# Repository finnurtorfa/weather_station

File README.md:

Weather Station
======

This is a git repository for the firmware and hardware of a weather station.

Specification:
----

The weather station should have the following capabilities:

- [x] Temperature measurement
- [x] Anemometer
- [ ] Wind direction measurement
- [x] Humidity measurement
- [x] Barometer 
- [x] Bluetooth Low Energy
- [ ] Serial communication
- [x] Battery powered

## Microcontroller

The microcontroller chosen to power the weather station is the Nordic
Semiconductor nRF51422 multiprotocol system on a chip microcontroller. It's key
features include

- 2.4 GHz transceiver
- ARM Cortex-M0 32 bit processor
- 256 or 128 kB flash program memory
- 16 or 32 kB RAM
- 31 GPIO pins
- 32 bit and 16 bit timers
- SPI
- TWI(I2C)
- 8-10 bit ADC
- UART
- Programmable Peripheral Interconnect
- Real Time Counter

It comes in a variety of packages, but the package chosen is the QFN48 package.
It also has quite flexible power management and can be supplied by voltage in
the range of 1.8V to 3.6V.

## Crystal

The crystal chosen for this project is the FA-20H series 16 MHz crystal by
EPSON. It has a frequency stability of +-10ppm, 8pF load capacitance and 80 Ohm
ESR. Following Nordic Semiconductor's white paper on selecting load capacitors
with the crystal and guestimating the stray pcb capacitance as ~3 pF we select C1=C2=12pF

## Voltage regulator

The regulator chosen to supply power to the MCU is LM3668 buck/boost dc-dc
converter by Texas Instruments. It is a single inductor converter with high
efficiency(~90% for loads from approx 3-4 mA - few hundred mA in auto mode),
making it ideal to power the nRF51 devices from a single LiPo cell.

## Battery charging

The MCP73831 single cell LiIon/LiPo battery charge management controller was
chosen for the task of charging the battery from USB(5V) power source.

## Temperature Sensor

The TMP112 digital temperature sensor has a temperature operating range from
-40°C - +125°C. It has an accuracy of 0.5% or 1% depending on the operating
range and a resolutionof 12 bits. It communicates with the host MCU via I2C.

## Humidity Sensor

The Si7013 is a humidity and temperature sensor with an operating range from
0-100% in relative humidity and -40°C - +125°C. It has an accuracy of +-3%
relative humidity and +-0.4°C for temperature and communicates with a host MCU
through I2C. 

## Barometer sensor

The BMP280 is a barometer that has a pressure range from ~300-1100hPa with
typical accuracy of +-1 hPa. It communicates with a host MCU through either I2C
or SPI.

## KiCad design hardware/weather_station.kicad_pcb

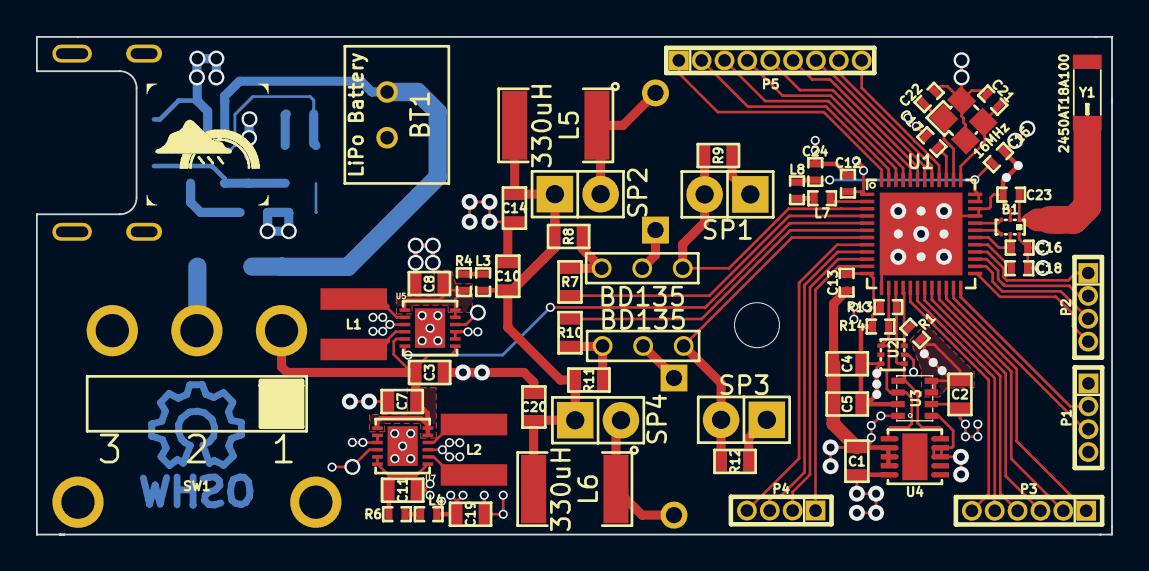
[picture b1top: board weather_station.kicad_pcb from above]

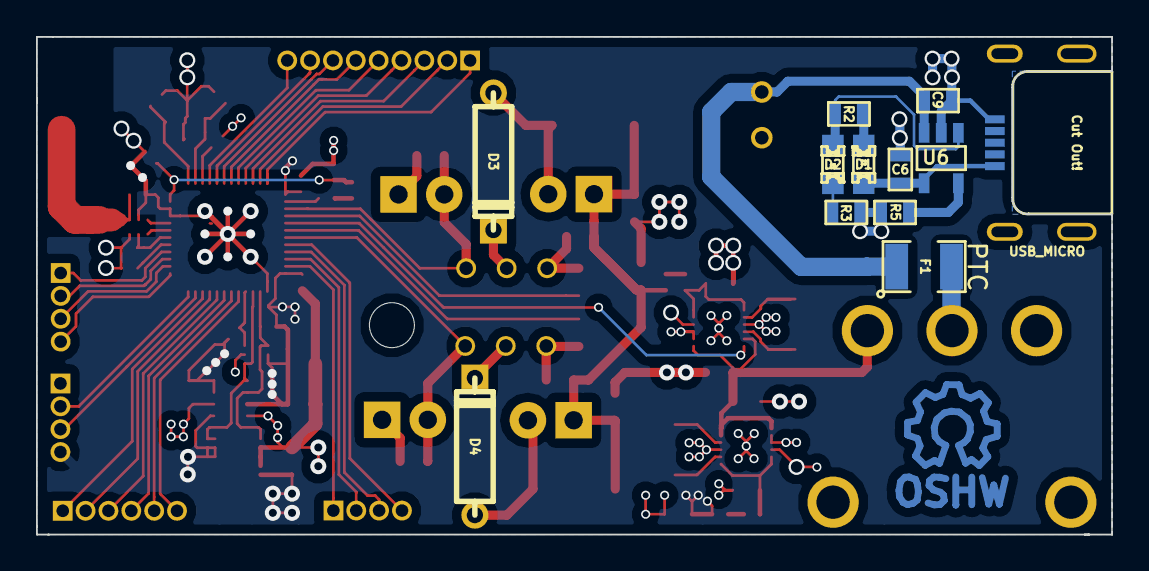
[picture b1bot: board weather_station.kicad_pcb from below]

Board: 4 copper layers, 59.7 x 27.6 mm, 78 parts (13 on the bottom side), 69 nets.

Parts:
B1: 2450BM14E0003; 2450BM14E0003Balun
BT1: LiPo Battery; JST_2_54
C1, C2, C4, C5, C10, C19: 100nF; SMD-0603
C3, C7: 10uF; SMD-0603
C6, C9: 4.7uF; SMD-0603
C8, C11, C14, C20: 22uF; SMD-0603
C12, C17: 100nF; SMD-0402
C13: 4.7uF; SMD-0402
C15: 1nF; SMD-0402
C16: 2.2nF; SMD-0402
C18: 47nF; SMD-0402
C21, C22: 12pF; SMD-0402
C23: 2pF; SMD-0402
C24: 1uF; SMD-0402
D1: RED; LED-0805
D2: GREEN; LED-0805
D3, D4: 1N4007; DO-41
F1: PTC; SMD-1210
J1: USB_MICRO; USB_MICRO_B
L1, L2: 2.2uH; SMD_4040
L3, L4: 52nH; SMD-0402
L5, L6: 330uH; SMD-1812
L7: 10uH; SMD-0402
L8: 15nH; SMD-0402
MountingHole_2-5mm: VAL**; MountingHole_2-5mm
P1, P2, P4: CONN_01X04; 4PIN_1.27MMP
P3: CONN_01X06; 6PIN_1.27MMP
P5: CONN_01X09; 9PIN_1.27MMP
Q1, Q2: BD135; TO-126
R1, R13, R14: 4K7; SMD-0402
R2, R3: 470R; SMD-0603
R4, R6: 10R; SMD-0402
R5: 2K; SMD-0603
R7, R10: 3K3; SMD-0603
R8, R11: 10K; SMD-0603
R9, R12: 33K; SMD-0603
SP1: SOUTH; Pin_Header_Straight_1x02
SP2: NORTH; Pin_Header_Straight_1x02
SP3: WEST; Pin_Header_Straight_1x02
SP4: EAST; Pin_Header_Straight_1x02
SW1: SWITCH_SPDT; T511006_SPDT
Symbol_OSHW-Logo_CopperTop: VAL**; Symbol_OSHW-Logo_CopperTop
U1: nRF51x22; nRF51_QFN48_HandSolder
U2: TMP112; SOT-563
U3: BMP280; LGA_2x2.5x0.95
U4: Si7013; DFN10_3x3
U5, U7: LM3668; WSON12_0.4P
U6: MCP73831; SOT-23-5-CUSTOM
X1: 16MHz; CRYSTAL_SMD2520
Y1: 2450AT18A100; 2450AT18A100E
weather_logo: weather_logo

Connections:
ALERT: R1.2, U1.16, U2.3
ANT1: B1.4, U1.31
ANT2: B1.3, U1.32
AVDD: C15.1, C24.1, L8.2, U1.35, U1.36
DCC: L7.1, U1.2
GND: B1.2, B1.6, BT1.2, C1.1, C2.1, C3.2, C4.2, C5.1, C6.2, C7.2, C8.2, C9.2, C10.2, C11.2, C12.2, C13.2, C14.2, C15.2, C16.1, C17.2, C18.2, C19.2, C20.2, C21.2, C22.1, C23.1, C24.2, J1.5, P1.4, R3.1, R5.1, R9.1, R12.1, SP1.1, SP3.1, U1.13, U1.33, U1.34, U2.2, U3.1, U3.7, U4.2, U4.3, U4.4, U5.3, U5.8, U5.9, U5.10, U5.~, U6.2, U7.3, U7.8, U7.9, U7.10, U7.~, X1.3
unnamed: B1.1, C23.2, Y1.1
unnamed: C6.1, D1.1, J1.1, U6.4
unnamed: C8.1, R4.2, U5.1, U5.11, U5.12
unnamed: C11.1, R6.2, U7.1, U7.11, U7.12
unnamed: C17.1, U1.39
unnamed: C18.1, U1.29
unnamed: D1.2, R2.1
unnamed: D2.1, R2.2, U6.1
unnamed: D2.2, R3.2
unnamed: D3.1, L5.1, SP2.2
unnamed: D3.2, Q1.2
unnamed: D4.1, L6.1, SP4.2
unnamed: D4.2, Q2.2
unnamed: F1.2, SW1.2
unnamed: L1.1, U5.2
unnamed: L1.2, U5.4
unnamed: L2.1, U7.2
unnamed: L2.2, U7.4
unnamed: L3.1, R4.1
unnamed: L4.1, R6.1
unnamed: L7.2, L8.1
unnamed: Q1.3, R7.1, R8.2
unnamed: Q2.3, R10.1, R11.2
unnamed: R5.2, U6.5
P0.04: P4.1, U1.8
P0.05: P4.2, U1.9
P0.06: P4.3, U1.10
P0.07: P4.4, U1.11
P0.11: P3.1, U1.17
P0.12: P3.2, U1.18
P0.13: P3.3, U1.19
P0.14: P3.4, U1.20
P0.15: P3.5, U1.21
P0.16: P3.6, U1.22
P0.17: P2.1, U1.25
P0.18: P2.2, U1.26
P0.19: P2.3, U1.27
P0.20: P2.4, U1.28
P0.21: P5.1, U1.40
P0.22: P5.2, U1.41
P0.23: P5.3, U1.42
P0.24: P5.4, U1.43
P0.25: P5.5, U1.44
P0.26: P5.6, U1.45
P0.27: P5.7, U1.46
P0.28: P5.8, U1.47
P0.29: P5.9, U1.48
PULSE1: Q1.1, R9.2, SP1.2, U1.3
PULSE2: Q2.1, R12.2, SP3.2, U1.7
PWM1: R7.2, U1.4
PWM2: R10.2, U1.6
SCL: R13.2, U1.15, U2.1, U3.4, U4.10
SDA: R14.2, U1.14, U2.4, U3.3, U4.1
SWDCLK: P1.3, U1.24
SWDIO: P1.2, U1.23
V3.3: C1.2, C2.2, C4.1, C5.2, C12.1, C13.1, C19.1, L4.2, P1.1, R1.1, R13.1, R14.1, U1.1, U1.12, U2.5, U2.6, U3.2, U3.5, U3.6, U3.8, U4.5, U4.8, U4.9
V5.0: C10.1, C14.1, C20.1, L3.2, L5.2, L6.2, R8.1, R11.1, SP2.1, SP4.1
V50_EN: U1.5, U5.6
VBAT: BT1.1, C9.1, F1.1, U6.3
VDD_PA: B1.5, C16.2, U1.30
VIN: C3.1, C7.1, SW1.1, U5.5, U5.7, U7.5, U7.6, U7.7
XC1: C21.1, U1.37, X1.2
XC2: C22.2, U1.38, X1.1

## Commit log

2015-03-27 Initial commit
    Add the README.md with the initial specification of the project and some description of
    the MCU chosen for the project.
2015-03-27 Datasheet and Product Anomaly Notification for MCU
    The MCU chosen is the nRF51422. Add the Product Specification and Product
    Anomaly Notification for it under reading material.
2015-03-27 KiCad project file
    Initialize the KiCad project.
2015-03-27 Add an empty schematic
2015-03-27 Add a ignore rules file for the hardware
    Ignore cache library files and backup files.
2015-03-27 Add a datasheet for LM3668 dc-dc regulator
    LM3668 is a 1A, High-Efficiency Dual-Mode Single-Inductor Buck-Boost DC-DC
    Converter.
2015-03-27 Application Note for LM3668 dc-dc regulator
2015-03-27 Add a nRF51x22 schematic symbol
2015-03-27 Add a battery to the schematic
    Along with a BAT+ label.
2015-03-28 Voltage regulator circuitry
    Add circuitry for the voltage regulator. The regulator chosen for the task is
    the LM3668 Buck/Boost converter by Texas Instruments. Also add a SPDT switch and
    a polyfuse to protect the circuitry against accidental short circuits.
2015-03-28 Datasheet for a SPDT switch.
    Add the datasheet for the chosesn SPDT switch. A 500 series right angle
    miniature slide switch.
2015-03-28 Add a spec sheet for the power inductor
    A 2.2 uH power inductor chosen for the LM3668 buck/boost converter.
2015-03-28 Add battery charging circuit
    Add circuitry around the MCP73831 linear charge management controller.
2015-03-28 Add decoupling circuitry and external LC filter
2015-03-28 Add circuitry for the 16MHz crystal
2015-03-28 Add a whitepaper about crystal oscillator circuitry
2015-03-29 Add datasheet for the crystal
2015-03-29 Move decoupling components around
2015-03-29 Add a datasheet for MCP73831 battery charge management controller
2015-03-29 Update the README with the core components
2015-03-29 Add datasheet for balun and antenna
    The balun is specifically designed for use with nRF51 devices.
2015-03-29 Add balun and an antenna to schematic
2015-03-30 Add TMP112 to the schematic and pull-up for TWI
    TMP112 is a temperature sensor made by Texas Instruments.
    Please note with the pull-up resistors that internally the GPIO pins of the
    nRF51 can be configured with an pull-up resistance of ~13K Ohm's so the
    external pull-up's might not be necessary.
    Also note that any GPIO pin can be selected as a TWI interface, so it is
    possible to update the schematic later to ease up the routing part.
2015-03-30 Add datasheet for the TMP112 temperature sensor
2015-03-30 Add Si7013 humidity and temperature sensor circuitry
2015-03-30 Add datasheet for Si7013
    And some minor additions to the temperature and humidity sensors.
2015-03-30 Add datasheet for BMP280 barometer sensor
2015-03-30 Add schematic circuitry for the BMP280
2015-03-30 Update the README file
    With information on the temperature sensor, humidity sensor and barometer sensor
    chosen for the station.
2015-04-05 Add a dc-dc buck/boost converter for 5V operation
2015-04-05 Add ultrasonic transmitter/receiver pair
    Two pairs to be exact, to be able to sense wind speed from North-South direction
    and East-West direction.
2015-04-07 Some minor modifications to the schematic
2015-04-07 Add a TO-126 footprint
2015-04-07 Add a components-to-footprints assignment file and netlist
2015-04-08 Add footprint for antenna
2015-04-08 Add footprint for balun
2015-04-08 Add footprint for Crystal
2015-04-08 Add footprint for Si7013
2015-04-08 Add footprint for diodes
2015-04-08 Add footprint for Pressure sensor
2015-04-08 Add SOT-23 footprint for battery management IC
2015-04-08 Add SOT-563 footprint for temperature sensor
2015-04-08 Add footprint for ultrasonic sensor
2015-04-08 Add WSON footprint for voltage regulator
2015-04-08 Add QFN48 footprint for nRF51
2015-04-09 Update the crystal smd footprint
2015-04-09 Add the battery connector footprint
2015-04-09 Add a footprint for the inductor for the voltage regulator
2015-04-09 Add footprint for the SPDT switch
2015-04-09 Add footprint for the USB Micro connector
2015-04-09 Update schematic and parts-to-footprint file
    With information on the footprints selected for the components.
2015-04-09 Update footprints net pad clearance
2015-04-09 Update ignore rules
2015-04-09 Add Layout file
    Related components have been grouped together!
2015-04-09 Update schematic with updated LM3668 component
2015-04-09 Update a capacitor footprint to 0603 instrad of 0402
2015-04-09 Update parts-to-footprint assignment
2015-04-09 Update layout. Place some groups of components strategically
2015-04-10 Update the footprint for the crystal again
2015-04-10 Place components around nRF51 device
2015-04-10 Group ultrasonic related components together
2015-04-10 Group together I2C components and related components
2015-04-10 Change the TWI pull-up resistors footprint to 0403
2015-04-10 Group the ultrasonic circuitry, the MCU circuitry and the TWI circuitry together
2015-04-11 Switch positions of pins on the nRF51
    Switch positions of PWM1-2 and PULSE1-2 and V50_EN pins on nRF51 to utilize the
    pins better and update the netlist as well.
2015-04-11 Update layout
    Group rest of components together, route all components together except the GND
    rail and the 3.3V rail.
2015-04-11 Add board outline
2015-04-12 Finish routing the board
2015-04-13 Add a programming header
2015-04-13 Add a header for pins P0.17-P0.20
2015-04-13 Add footprint for headers and route
    Add a 1.27mm pitched footprint for headers, add them to the pcb and route.
2015-04-13 Add a header for the south side GPIO's
2015-04-13 Add header and route the south side gpio's
2015-04-13 Add header for west side GPIO's
2015-04-13 Add footprint and route west side GPIO's
2015-04-13 Add header for north side GPIO's
2015-04-13 Add footprint for northside gpio's and routing
2015-04-13 Add svg images
    For each of the layers and the top and bottom silkscreen layers plus one image
    of all of the layers on a single image.
2015-04-18 Change footprint of ultrasonic sensor and I2C change
    Connect the SDO pin of barometer to 3.3V instead of GND
2015-04-19 Reroute entire PCB
    Smaller, faster, better.. Pick one of 2 ;)
2015-04-19 Update images and add a schematic as well
2015-04-20 Add footprint for a logo
2015-04-20 Add the weather logo footprint to the layout
